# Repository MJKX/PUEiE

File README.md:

# PUEiE

Completed project uploaded in catalog "completed_project".

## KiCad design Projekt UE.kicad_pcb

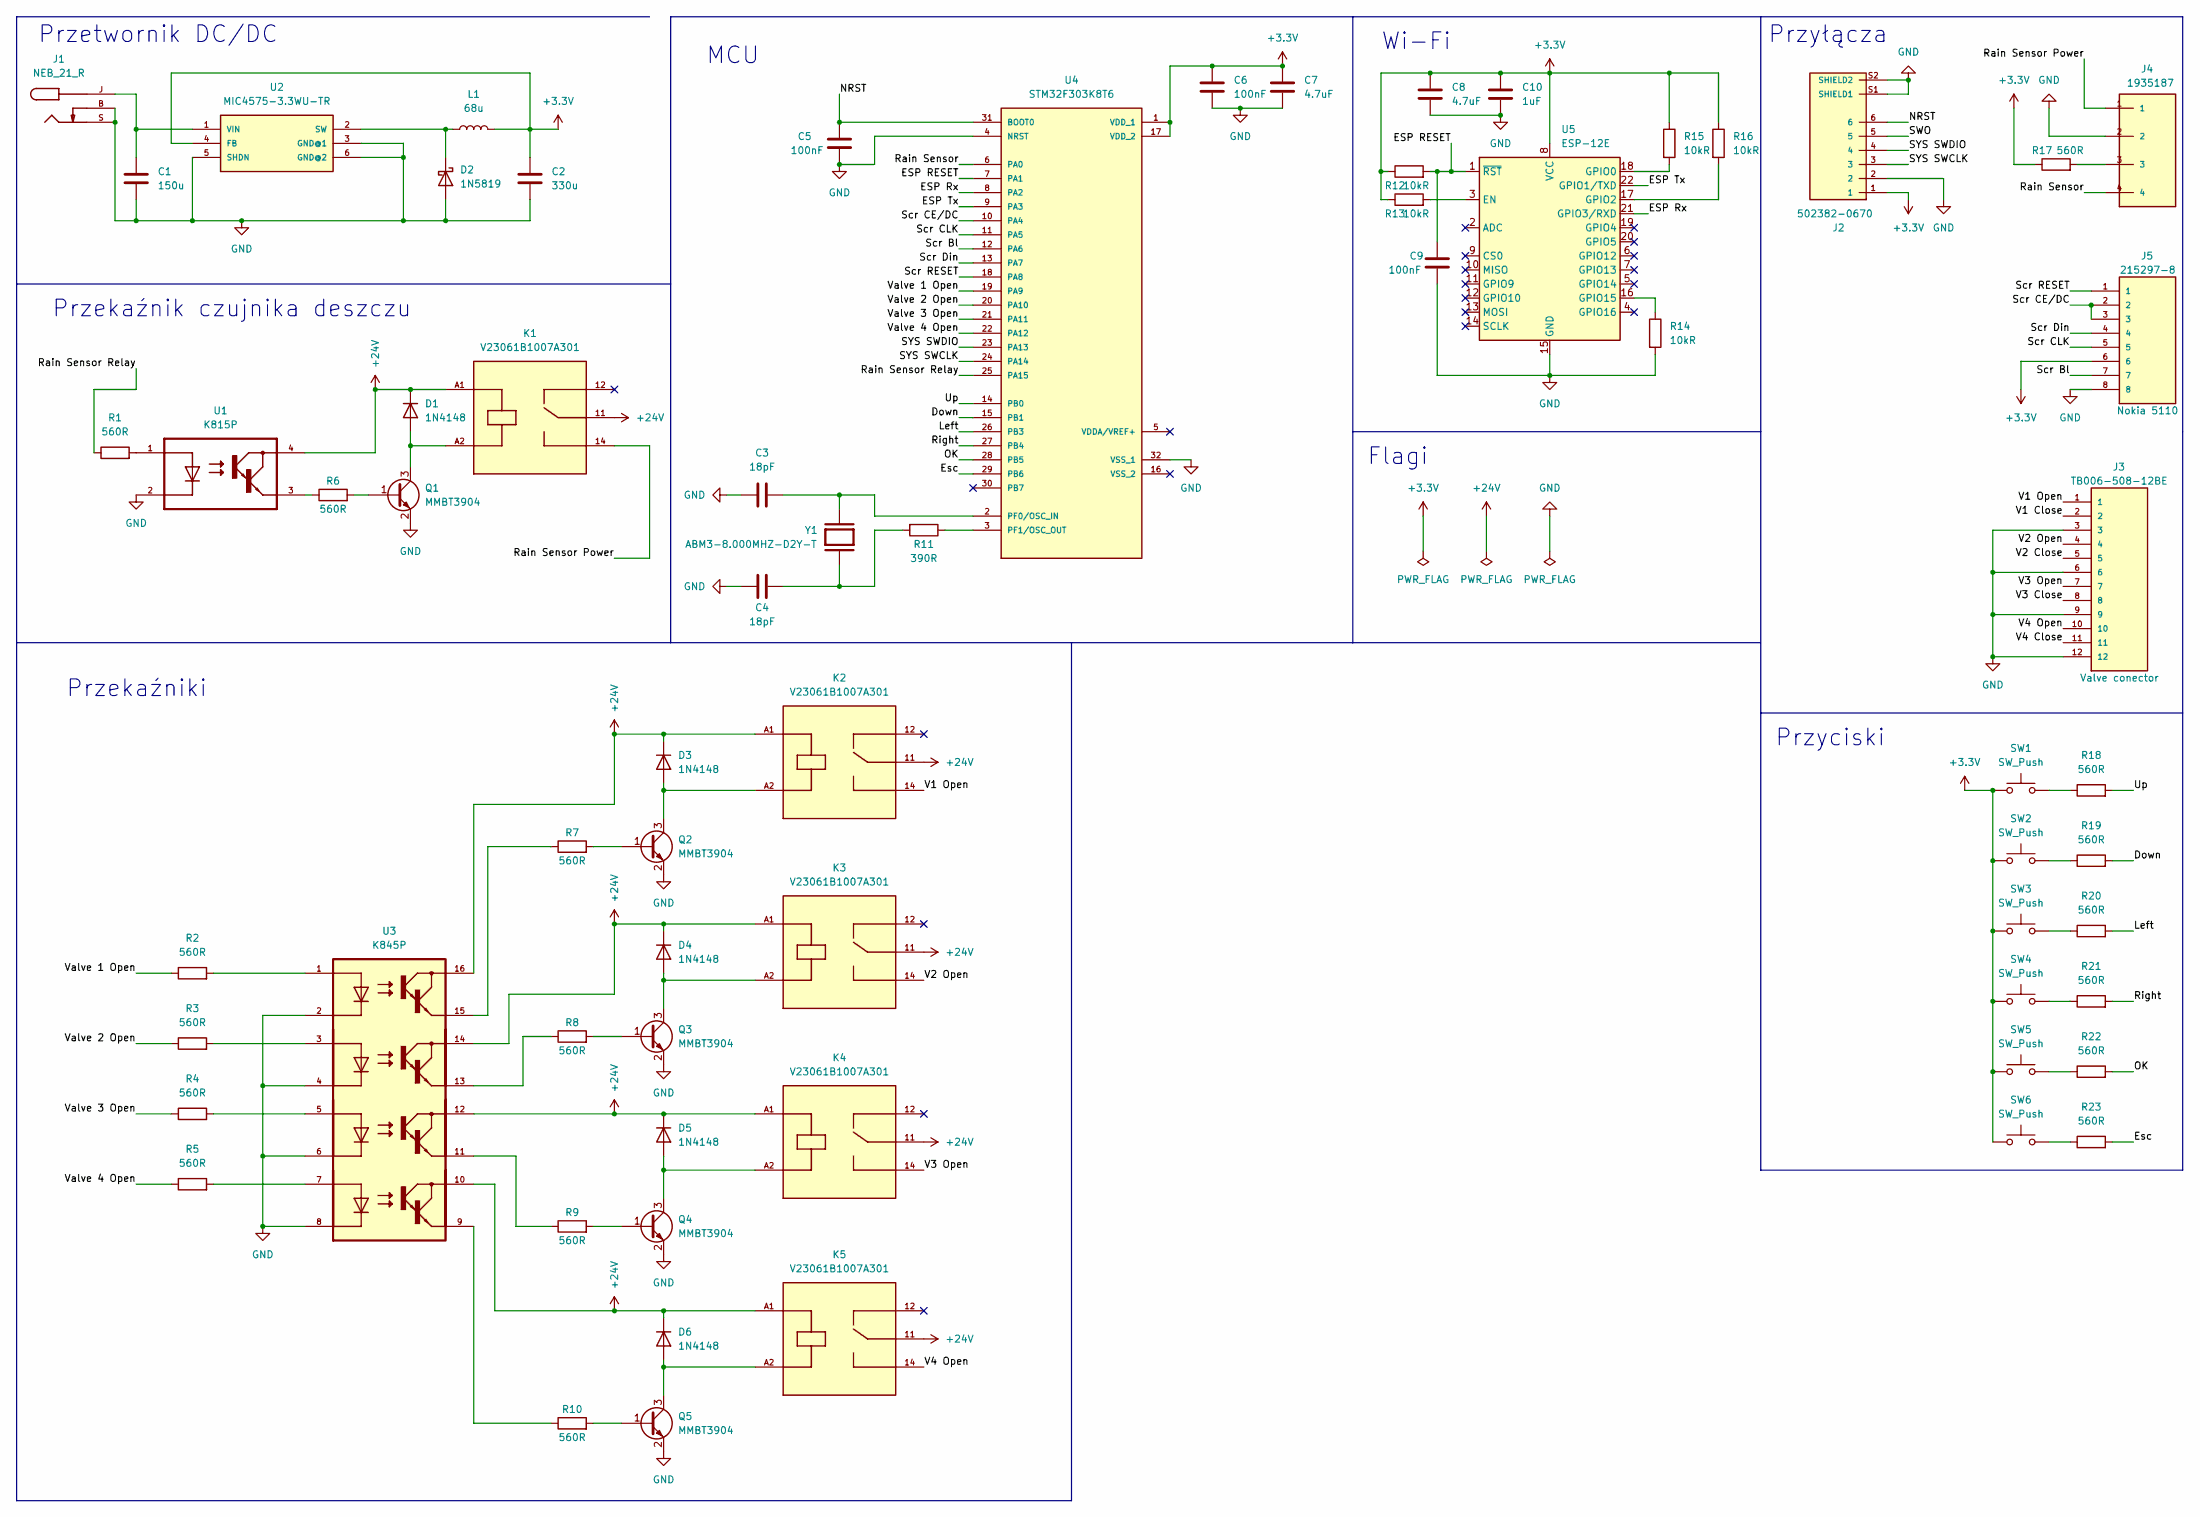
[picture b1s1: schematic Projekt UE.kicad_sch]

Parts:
C1: 150u; CP_Radial_D8.0mm_P3.50mm
C2: 330u; CP_Radial_D8.0mm_P3.50mm
C3, C4: 18pF; C_Disc_D6.0mm_W2.5mm_P5.00mm
C5, C6, C9: 100nF; C_Disc_D10.5mm_W5.0mm_P5.00mm
C7, C8: 4.7uF; CP_Radial_D8.0mm_P3.50mm
C10: 1uF; CP_Radial_D5.0mm_P2.00mm
D1, D3, D4, D5, D6: 1N4148; D_DO-35_SOD27_P7.62mm_Horizontal
D2: 1N5819; D_DO-41_SOD81_P10.16mm_Horizontal
J1: NEB_21_R; LUMBERG_NEB_21_R; PARTREV 01/2018
J2: 502382-0670; MOLEX_5023820670; PARTREV F
J3: TB006-508-12BE; CUI_TB006-508-12BE
J4: 1935187
J5: 215297-8; TE_215297-8; PARTREV R
K1, K2, K3, K4, K5: V23061B1007A301; RELAY_1-1393223-7; PARTREV 0611
L1: 68u; L_Radial_D24.4mm_P23.70mm_Murata_1400series
Q1, Q2, Q3, Q4, Q5: MMBT3904; SOT-23
R1, R2, R3, R4, R5, R6, R7, R8, R9, R10, R17, R18, R19, R20, R21, R22, R23: 560R; R_1206_3216Metric
R11: 390R; R_1206_3216Metric
R12, R13, R14, R15, R16: 10kR; R_1206_3216Metric
SW1, SW2, SW3, SW4, SW5, SW6: SW_Push; SW_Push_2P1T_Toggle_CK_PVA1xxH1xxxxxxV2
U1: K815P; DIP762W50P254L977H451Q8
U2: MIC4575-3.3WU-TR; TO170P1524X460-6N
U3: K845P; DIP762W51P254L1992H425Q16
U4: STM32F303K8T6; QFP80P900X900X160-32N
U5: ESP-12E
Y1: ABM3-8.000MHZ-D2Y-T; XTAL_ABM3-8.000MHZ-D2Y-T; PARTREV 4/25/2022

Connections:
+3.3V: C2.1, C6.1, C7.1, C8.1, C10.1, J2.1, J5.6, L1.2, R12.1, R13.1, R15.1, R16.1, R17.1, SW1.1, SW2.1, SW3.1, SW4.1, SW5.1, SW6.1, U2.4 (FB), U4.1 (VDD_1), U4.17 (VDD_2), U5.8 (VCC)
+24V: D1.1 (K), D3.1 (K), D4.1 (K), D5.1 (K), D6.1 (K), K1.11, K1.A1, K2.11, K2.A1, K3.11, K3.A1, K4.11, K4.A1, K5.11, K5.A1, U1.4, U3.10, U3.12, U3.14, U3.16
/Down: R19.2, U4.15 (PB1)
/ESP RESET: C9.1, R12.2, U4.7 (PA1), U5.1 (~RST)
/ESP Rx: U4.8 (PA2), U5.21 (GPIO3/RXD)
/ESP Tx: U4.9 (PA3), U5.22 (GPIO1/TXD)
/Esc: R23.2, U4.29 (PB6)
/Left: R20.2, U4.26 (PB3)
/NRST: C5.1, J2.6, U4.31 (BOOT0)
/OK: R22.2, U4.28 (PB5)
/Rain Sensor: J4.4, U4.6 (PA0)
/Rain Sensor Power: J4.1, K1.14
/Rain Sensor Relay: R1.1, U4.25 (PA15)
/Right: R21.2, U4.27 (PB4)
/SWO: J2.5
/SYS SWCLK: J2.3, U4.24 (PA14)
/SYS SWDIO: J2.4, U4.23 (PA13)
/Scr Bl: J5.7, U4.12 (PA6)
/Scr CE/DC: J5.2, J5.3, U4.10 (PA4)
/Scr CLK: J5.5, U4.11 (PA5)
/Scr Din: J5.4, U4.13 (PA7)
/Scr RESET: J5.1, U4.18 (PA8)
/Up: R18.2, U4.14 (PB0)
/V1 Close: J3.2
/V1 Open: J3.1, K2.14
/V2 Close: J3.5
/V2 Open: J3.4, K3.14
/V3 Close: J3.8
/V3 Open: J3.7, K4.14
/V4 Close: J3.11
/V4 Open: J3.10, K5.14
/Valve 1 Open: R2.1, U4.19 (PA9)
/Valve 2 Open: R3.1, U4.20 (PA10)
/Valve 3 Open: R4.1, U4.21 (PA11)
/Valve 4 Open: R5.1, U4.22 (PA12)
GND: C1.2, C2.2, C3.1, C4.1, C5.2, C6.2, C7.2, C8.2, C9.2, C10.2, D2.2 (A), J1.B, J1.S, J2.2, J2.S1 (SHIELD1), J2.S2 (SHIELD2), J3.3, J3.6, J3.9, J3.12, J4.2, J5.8, Q1.2 (E), Q2.2 (E), Q3.2 (E), Q4.2 (E), Q5.2 (E), R14.2, U1.2, U2.3 (GND@1), U2.5 (SHDN), U2.6 (GND@2), U3.2, U3.4, U3.6, U3.8, U4.4 (NRST), U4.32 (VSS_1), U5.15 (GND)
unnamed: C1.1, J1.J, U2.1 (VIN)
unnamed: C3.2, U4.2 (PF0/OSC_IN), Y1.1
unnamed: C4.2, R11.2, Y1.2
unnamed: D1.2 (A), K1.A2, Q1.3 (C)
unnamed: D2.1 (K), L1.1, U2.2 (SW)
unnamed: D3.2 (A), K2.A2, Q2.3 (C)
unnamed: D4.2 (A), K3.A2, Q3.3 (C)
unnamed: D5.2 (A), K4.A2, Q4.3 (C)
unnamed: D6.2 (A), K5.A2, Q5.3 (C)
unnamed: J4.3, R17.2
unnamed: Q1.1 (B), R6.2
unnamed: Q2.1 (B), R7.2
unnamed: Q3.1 (B), R8.2
unnamed: Q4.1 (B), R9.2
unnamed: Q5.1 (B), R10.2
unnamed: R1.2, U1.1
unnamed: R2.2, U3.1
unnamed: R3.2, U3.3
unnamed: R4.2, U3.5
unnamed: R5.2, U3.7
unnamed: R6.1, U1.3
unnamed: R7.1, U3.15
unnamed: R8.1, U3.13
unnamed: R9.1, U3.11
unnamed: R10.1, U3.9
unnamed: R11.1, U4.3 (PF1/OSC_OUT)
unnamed: R13.2, U5.3 (EN)
unnamed: R14.1, U5.16 (GPIO15)
unnamed: R15.2, U5.18 (GPIO0)
unnamed: R16.2, U5.17 (GPIO2)
unnamed: R18.1, SW1.2
unnamed: R19.1, SW2.2
unnamed: R20.1, SW3.2
unnamed: R21.1, SW4.2
unnamed: R22.1, SW5.2
unnamed: R23.1, SW6.2

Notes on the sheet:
Przekaźnik czujnika deszczu
Przekaźniki
Flagi
Przyciski
Przetwornik DC/DC
Wi-Fi
MCU
Przyłącza

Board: 2 copper layers, 67 parts (0 on the bottom side), 67 nets, no tracks yet.

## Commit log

2022-11-04 system nawadniania
2022-12-11 Update project.
2022-12-11 Connect VDD_2 with VDD_1
2022-12-11 Upload pcb after load footprint
2023-01-21 PUEiE - Last version
2023-01-21 final version of the project
